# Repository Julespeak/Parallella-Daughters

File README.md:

# Parallella-Daughters
Daughterboard designs for ADC front end of the Parallella

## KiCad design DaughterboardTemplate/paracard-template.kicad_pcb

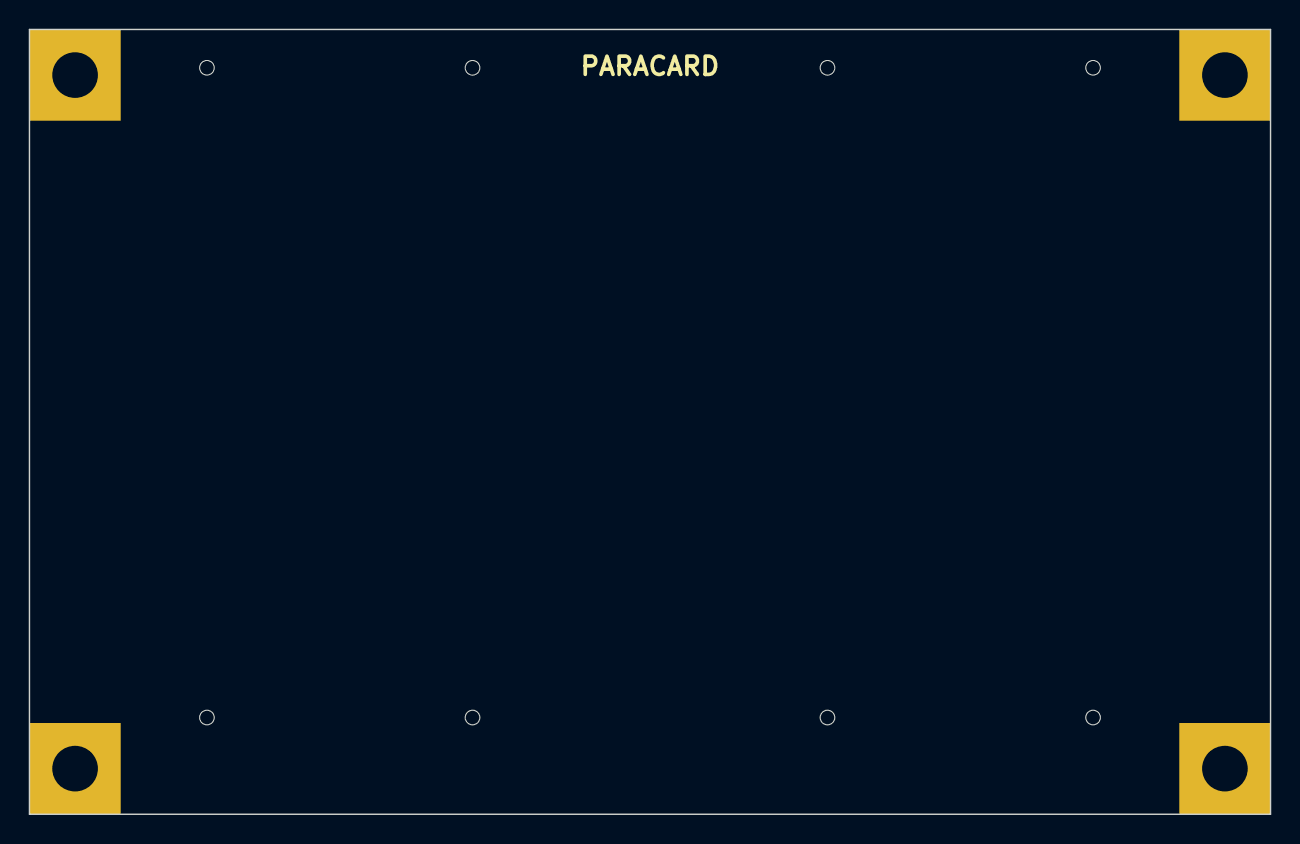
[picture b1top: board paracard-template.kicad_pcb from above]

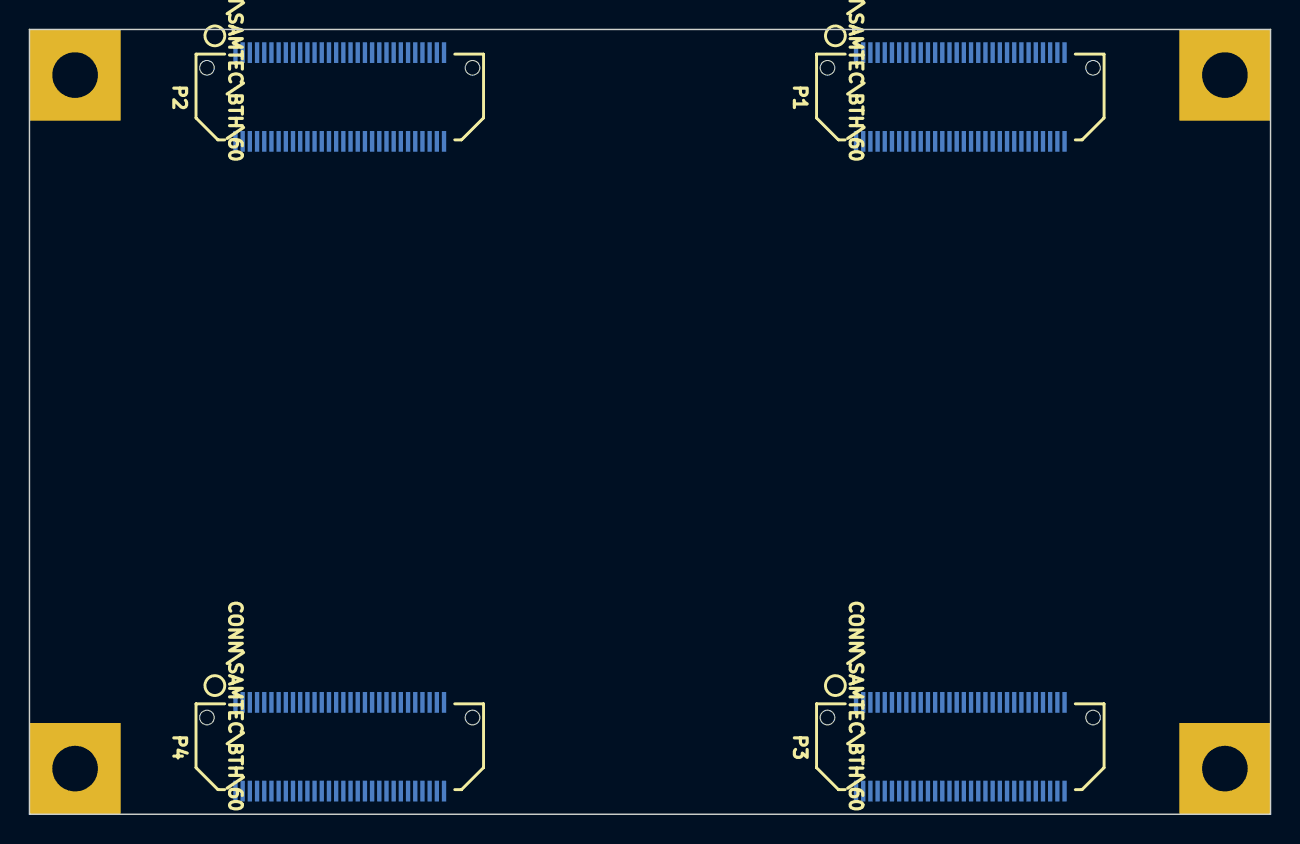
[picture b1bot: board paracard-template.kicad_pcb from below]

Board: 2 copper layers, 86.4 x 54.6 mm, 8 parts (4 on the bottom side), 14 nets, no tracks yet.

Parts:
MH1, MH2, MH3, MH4: MTG\PTH\125\SQ; MTG_PTH_125_SQ
P1, P2, P3, P4: CONN\SAMTEC\BTH\60; CONN_SAMTEC_BTH_60

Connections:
/NORTH/VDDIO: P2.1, P2.2
/POWER/1P0V: P3.43, P3.44
/POWER/1P8V: P3.49, P3.50
/POWER/1P35V: P3.47, P3.48
/POWER/2P5V: P3.57, P3.58
/POWER/3P3V: P3.59, P3.60
/POWER/SYS_5P0V: P3.1, P3.2
/POWER/VDD_ADJ: P3.53, P3.54
/POWER/VDD_DSP: P3.45, P3.46
/POWER/VDD_GPIO: P3.55, P3.56
/SOUTH/VDDIO: P4.1, P4.2
GND: MH2.1, MH3.1, MH4.1, P1.11, P1.12, P1.21, P1.22, P1.31, P1.32, P1.41, P1.42, P1.51, P1.52, P2.12, P2.22, P2.32, P2.42, P2.52, P3.11, P3.12, P3.21, P3.22, P3.31, P3.32, P3.35, P3.36, P3.41, P3.42, P3.51, P3.52, P4.12, P4.22, P4.32, P4.42, P4.52
unnamed: P2.11, P2.21, P2.31, P2.41, P2.51
unnamed: P4.11, P4.21, P4.31, P4.41, P4.51

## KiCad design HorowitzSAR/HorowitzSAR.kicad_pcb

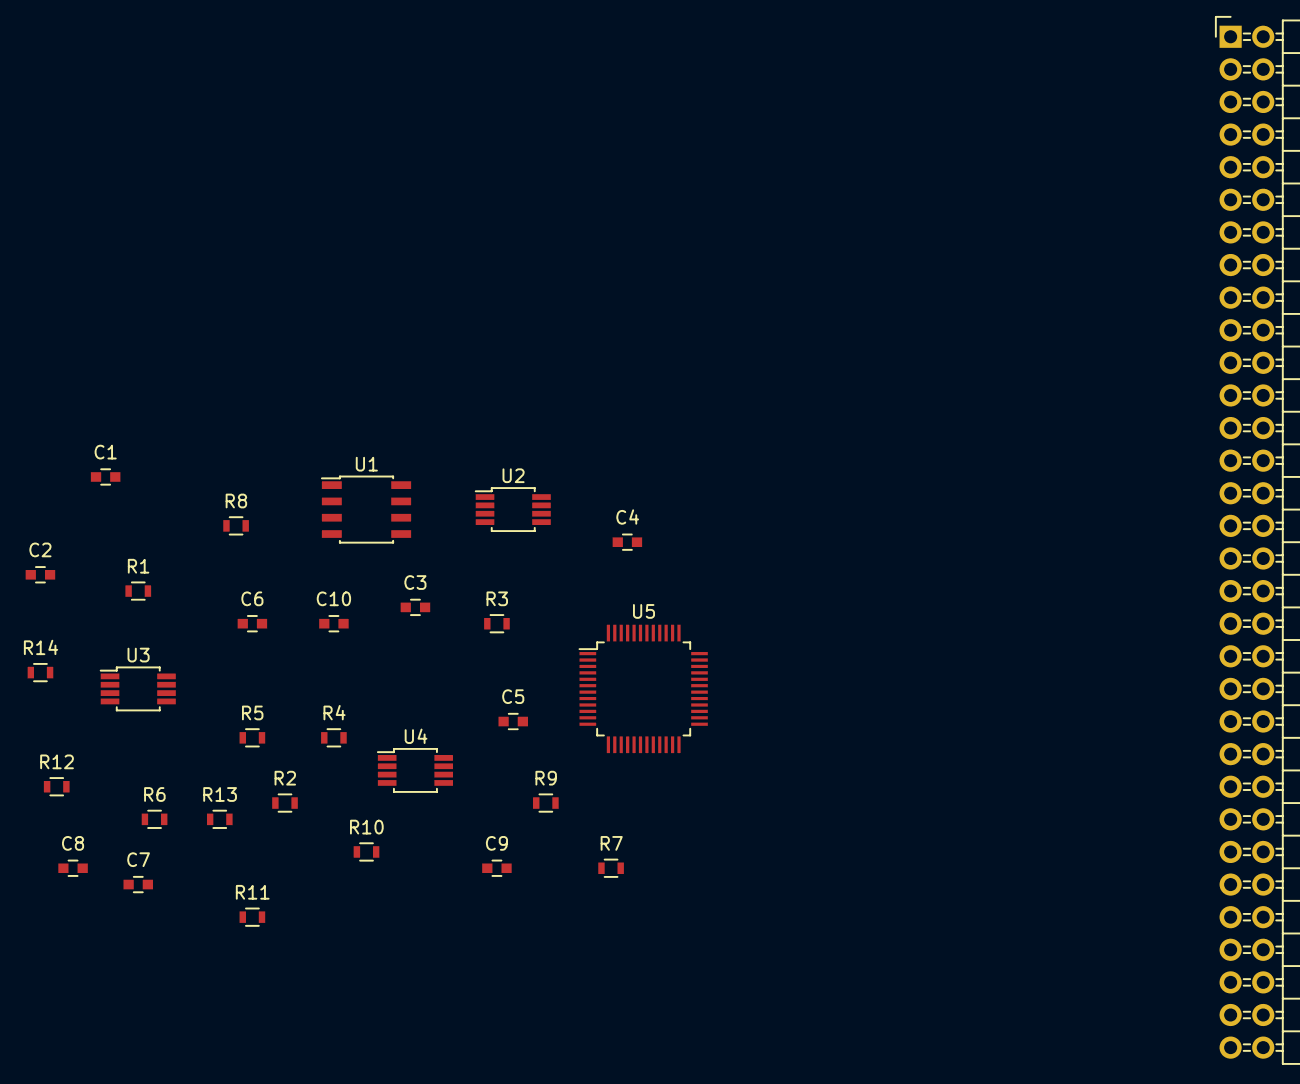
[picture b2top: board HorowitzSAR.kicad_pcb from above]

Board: 2 copper layers, 30 parts (0 on the bottom side), 23 nets, no tracks yet.

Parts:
C1, C10: 0.1 uF; C_0603
C2: 100 pF; C_0603
C3, C4: 10 pF; C_0603
C5: 33 pF; C_0603
C6: 1 uF; C_0603
C7, C8: 2.7 nF; C_0603
C9: 10 uF; C_0603
P1: C64AC; Pin_Header_Angled_2x32
R1: 332; R_0603
R2: 200; R_0603
R3: 249; R_0603
R4: 54.9; R_0603
R5: 49.9; R_0603
R6, R7, R10: 499; R_0603
R8, R13: 1K; R_0603
R9: 665; R_0603
R11, R12: 15; R_0603
R14: 120; R_0603
U1: ISL21007B-25; SOIC-8_3.9x4.9mm_Pitch1.27mm
U2, U3: AD8021; MSOP-8_3x3mm_Pitch0.65mm
U4: AD8031; MSOP-8_3x3mm_Pitch0.65mm
U5: AD7641; LQFP-48_7x7mm_Pitch0.5mm

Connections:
+2V5: C10.1, U5.2, U5.6, U5.7, U5.19, U5.44, U5.47, U5.48
+4V5: U1.2, U2.7, U3.7, U4.7
-2V: C3.2, C4.2, U2.4, U3.4
GND: C1.2, C2.2, C6.2, C7.2, C8.2, C9.2, C10.2, R3.2, R6.1, U1.1, U1.4, U4.4, U5.1, U5.17, U5.36, U5.38, U5.41, U5.42
GNDD: U5.3, U5.4, U5.20, U5.30, U5.33, U5.34
INPUT: R1.1, R2.1
unnamed: C1.1, R3.1, R4.1, R7.1
unnamed: C2.1, R2.2, R5.1
unnamed: C3.1, U2.5
unnamed: C4.1, U3.5
unnamed: C5.1, R1.2, R9.1, U2.2
unnamed: C5.2, R9.2, R12.1, U2.6
unnamed: C6.1, R8.1, U4.3
unnamed: C7.1, R11.2, U5.43
unnamed: C8.1, R12.2, U5.39
unnamed: C9.1, R14.2, U5.37
unnamed: R4.2, U2.3
unnamed: R5.2, U3.3
unnamed: R8.2, U1.6
unnamed: R6.2, R10.1, U3.2
unnamed: R10.2, R11.1, U3.6
unnamed: R7.2, R13.1, R14.1, U4.6
unnamed: R13.2, U4.2

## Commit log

2015-11-16 Forgot to add files to git
2015-11-25 Added daughterboard template
